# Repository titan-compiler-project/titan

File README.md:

# Titan

Visit the docs at https://titan-compiler-project.github.io/titan/ for more information.

Please look at ``CITATION.cff`` or the citation tools on GitHub for how to cite this repository properly :)

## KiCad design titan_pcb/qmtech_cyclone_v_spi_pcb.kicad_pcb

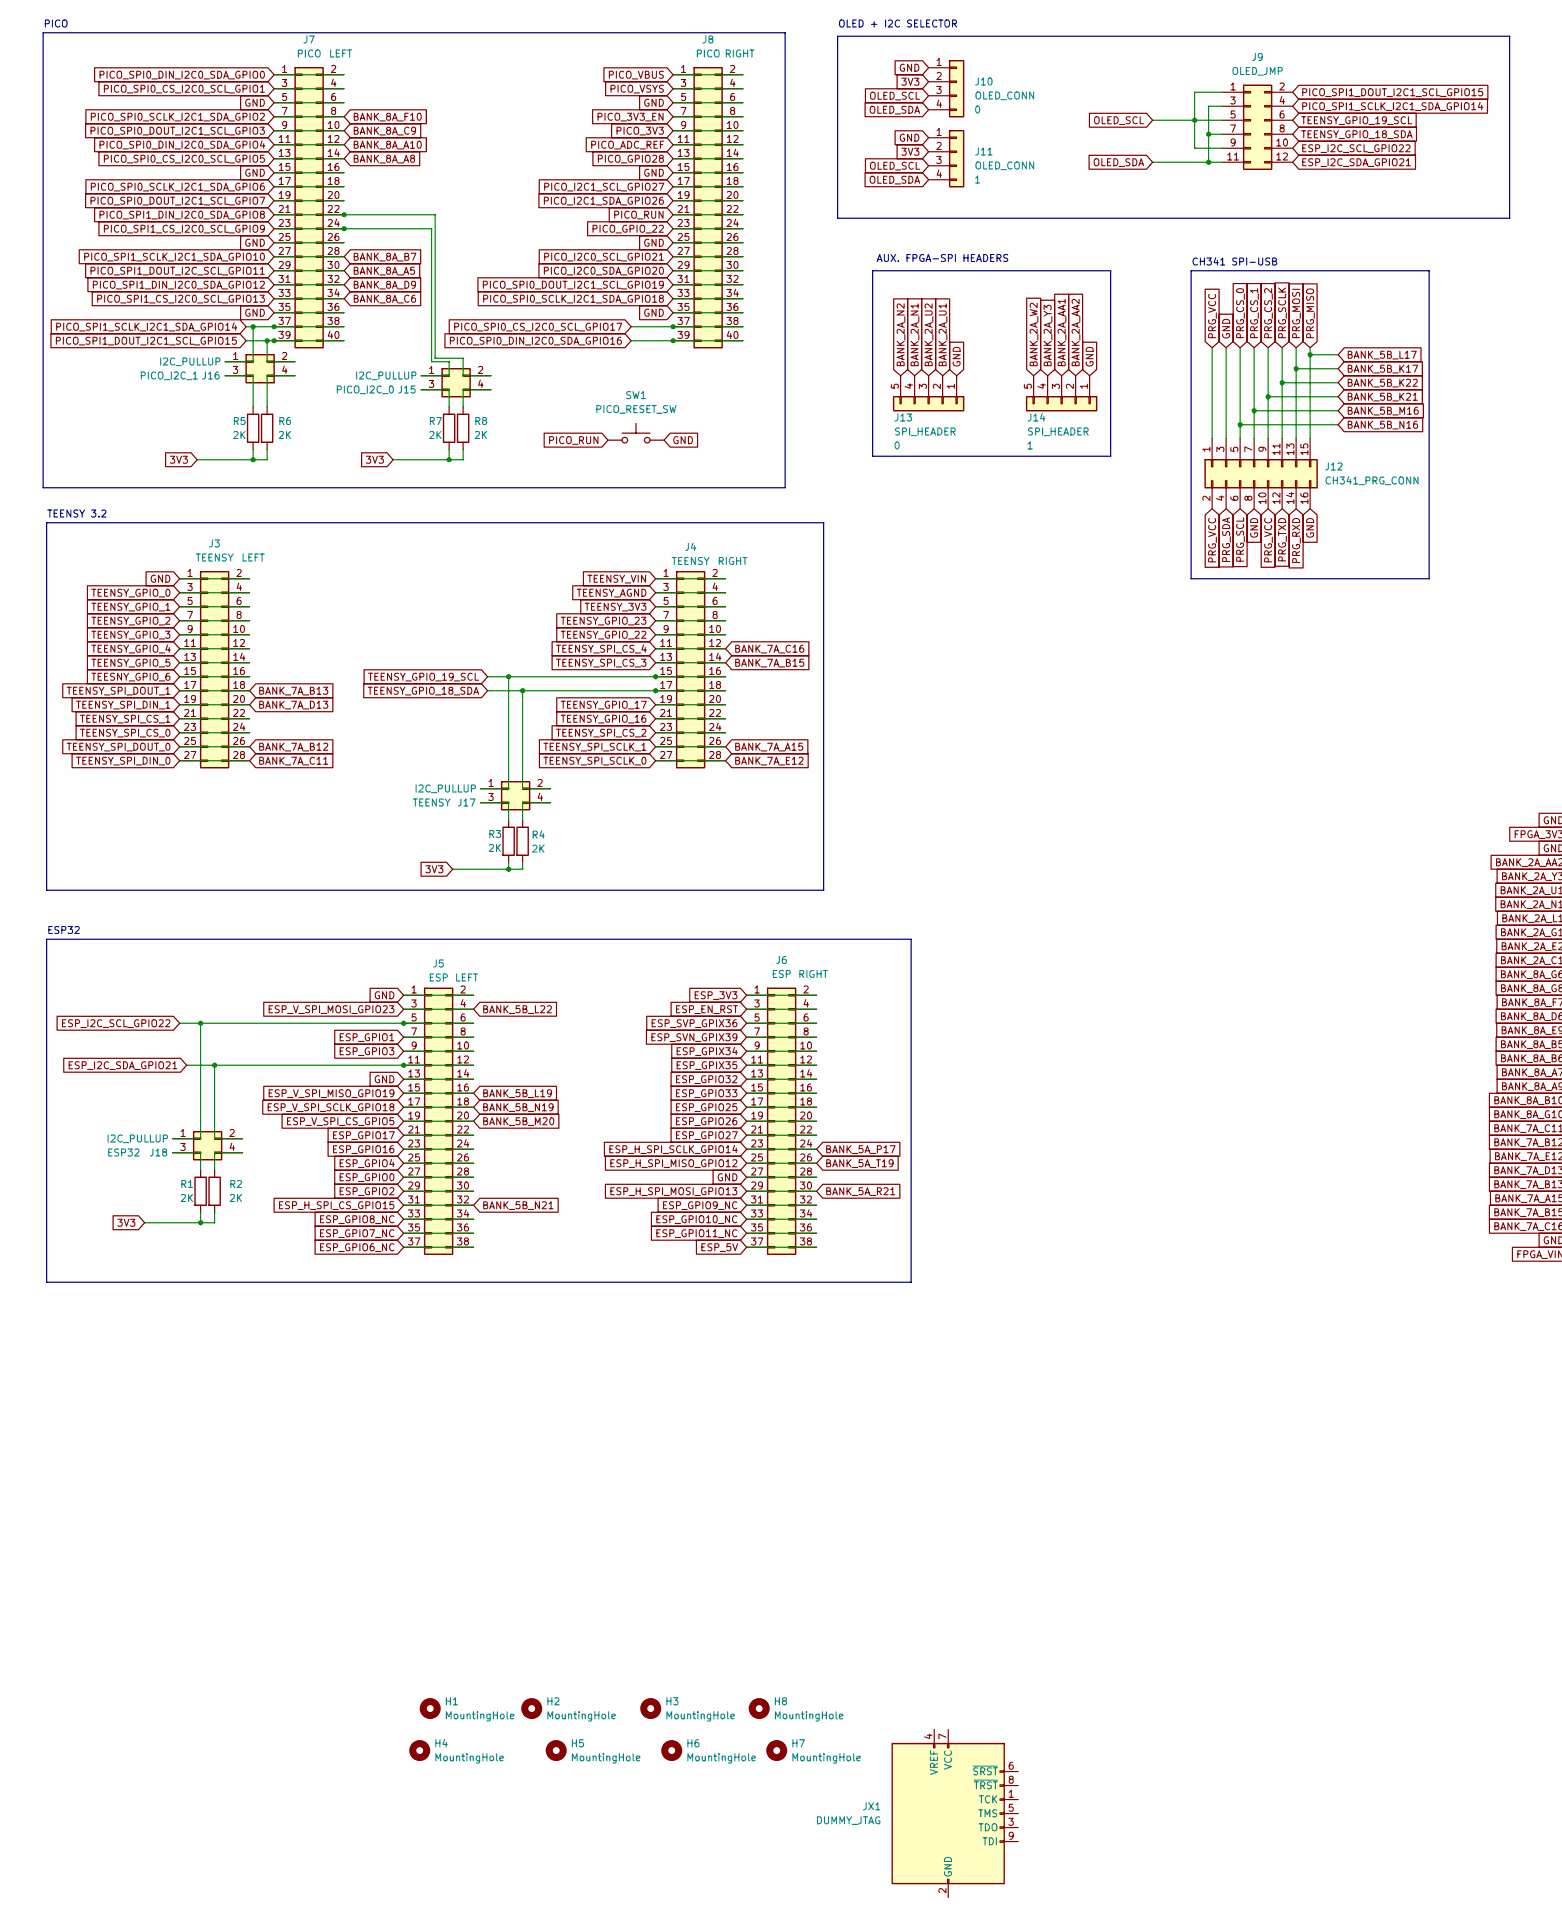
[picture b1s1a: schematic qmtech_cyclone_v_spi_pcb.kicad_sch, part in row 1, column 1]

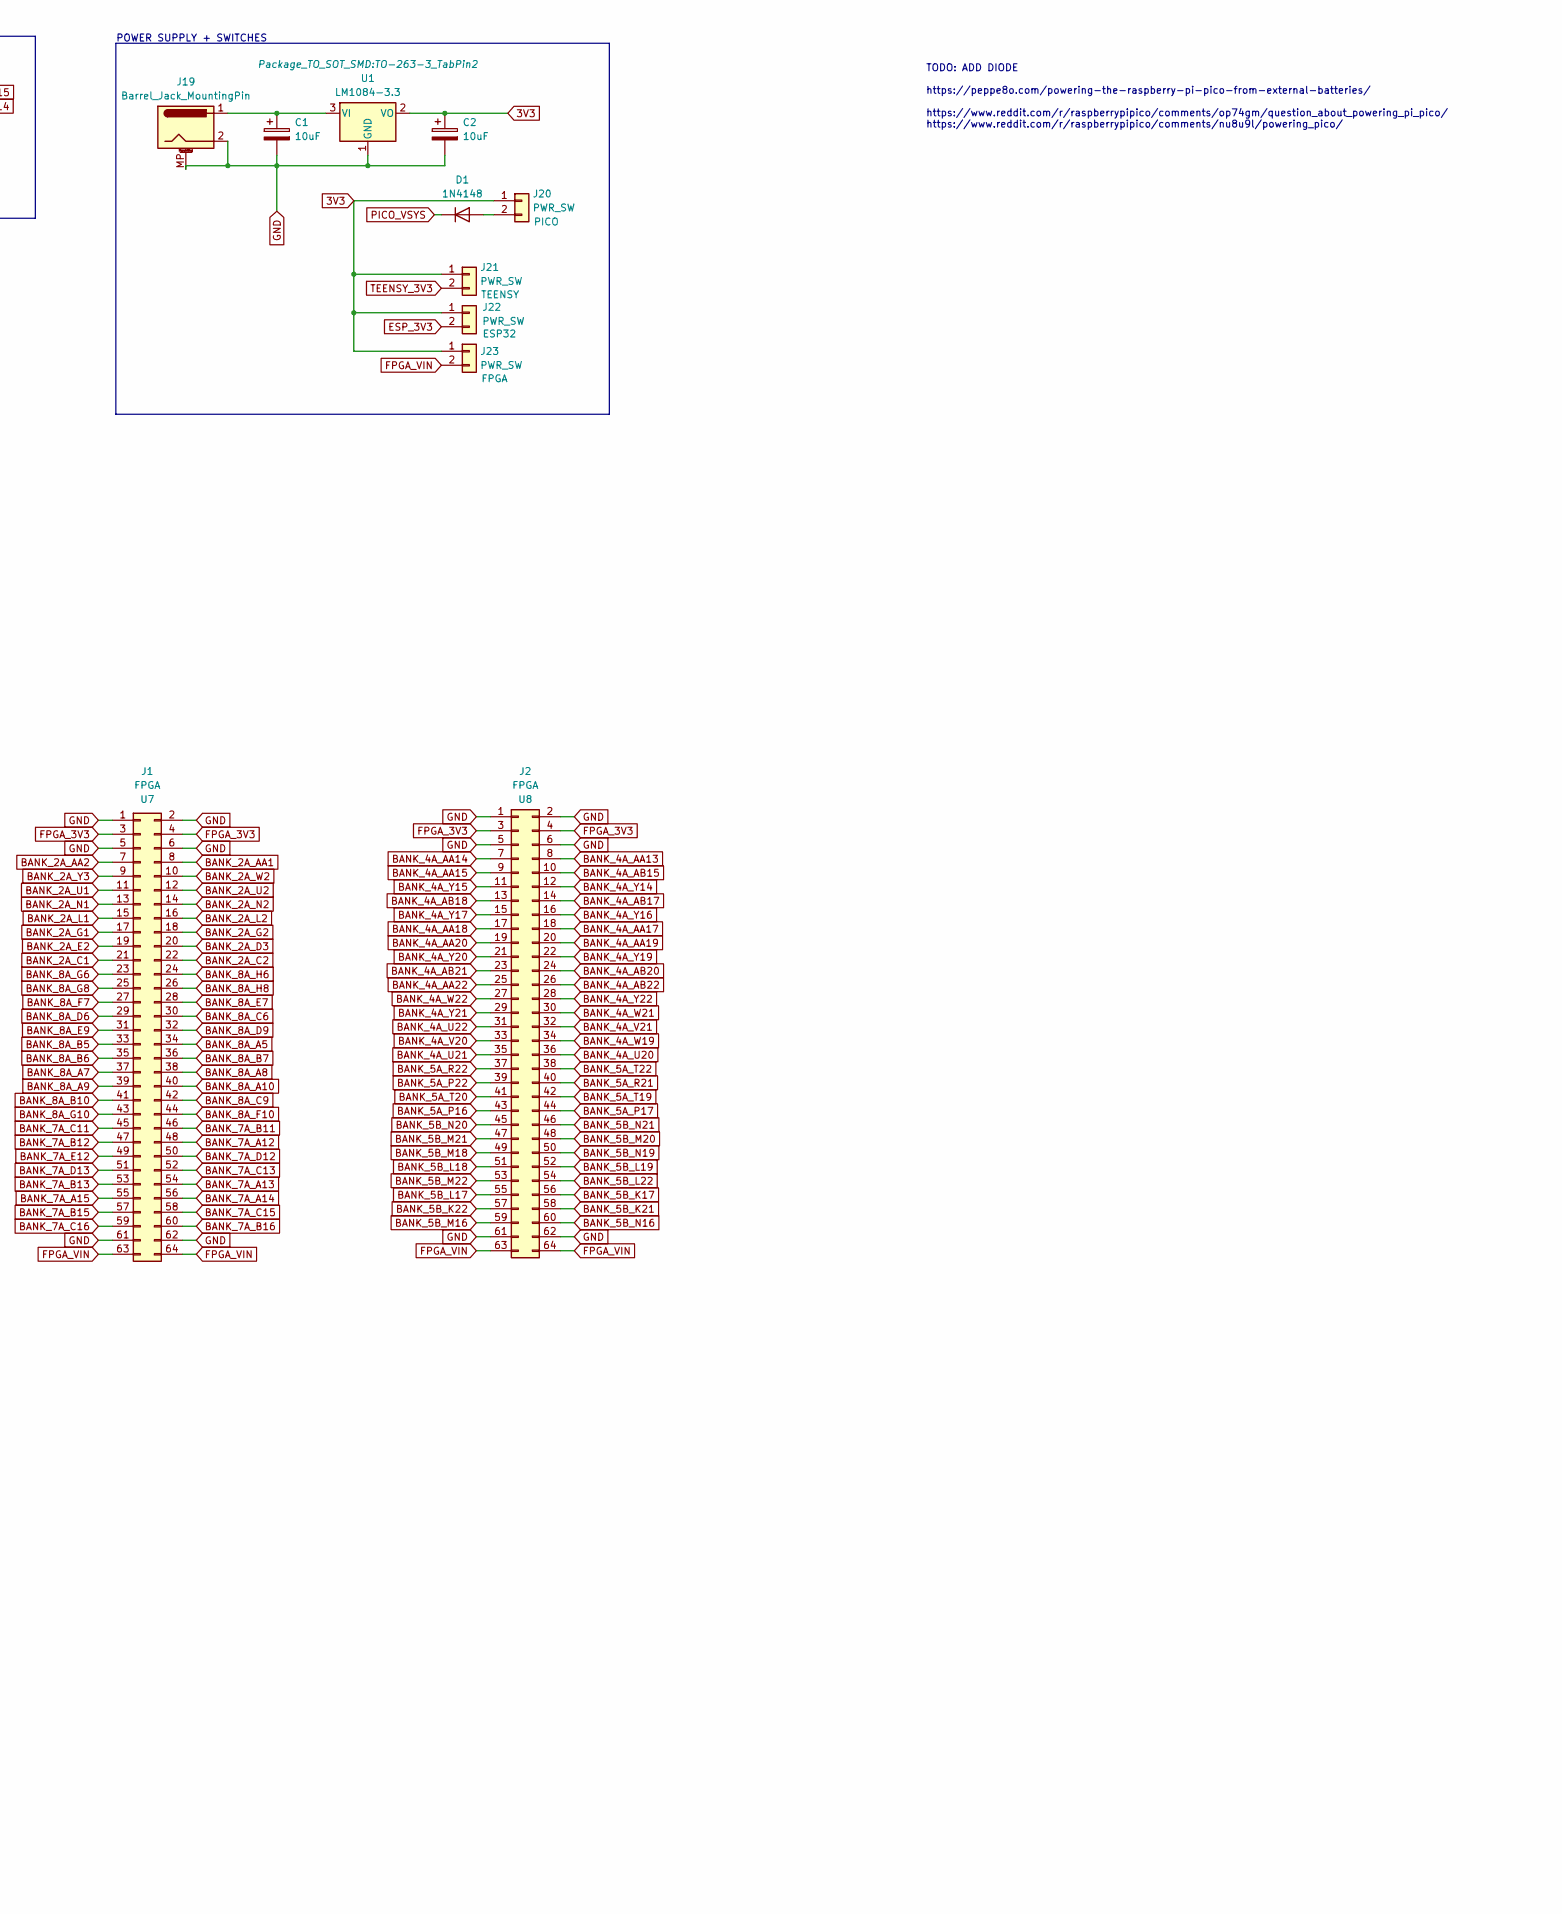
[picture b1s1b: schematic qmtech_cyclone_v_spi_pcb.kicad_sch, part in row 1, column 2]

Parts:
C1, C2: 10uF; CP_EIA-3216-18_Kemet-A_Pad1.58x1.35mm_HandSolder
D1: 1N4148; D_DO-35_SOD27_P7.62mm_Horizontal
H1, H2, H3, H4, H5, H6, H7, H8: MountingHole; MountingHole_2.2mm_M2_ISO7380_Pad_TopBottom
J1, J2: FPGA; PinHeader_2x32_P2.54mm_Vertical
J3, J4: TEENSY; PinSocket_2x14_P2.54mm_Vertical
J5, J6: ESP; PinSocket_2x19_P2.54mm_Vertical
J7, J8: PICO; PinSocket_2x20_P2.54mm_Vertical
J9: OLED_JMP; PinHeader_2x06_P2.54mm_Vertical
J10, J11: OLED_CONN; PinSocket_1x04_P2.54mm_Vertical
J12: CH341_PRG_CONN; PinSocket_2x08_P2.54mm_Vertical
J13, J14: SPI_HEADER; PinHeader_1x05_P2.54mm_Vertical
J15, J16, J17, J18: I2C_PULLUP; PinHeader_2x02_P2.54mm_Vertical
J19: Barrel_Jack_MountingPin; BarrelJack_CUI_PJ-063AH_Horizontal
J20, J21, J22, J23: PWR_SW; PinHeader_1x02_P2.54mm_Vertical
JX1: DUMMY_JTAG; IDC-Header_2x05_P2.54mm_Vertical
R1, R2, R3, R4, R5, R6, R7, R8: 2K; R_1206_3216Metric_Pad1.30x1.75mm_HandSolder
SW1: PICO_RESET_SW; SW_PUSH_6mm_H5mm
U1: LM1084-3.3; TO-263-3_TabPin2

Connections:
3V3: C2.1, J10.2, J11.2, J20.1, J21.1, J22.1, J23.1, R1.2, R2.2, R3.2, R4.2, R5.2, R6.2, R7.2, R8.2, U1.2 (VO)
BANK_2A_AA1: J1.8, J14.3
BANK_2A_AA2: J1.7, J14.2
BANK_2A_C1: J1.21
BANK_2A_C2: J1.22
BANK_2A_D3: J1.20
BANK_2A_E2: J1.19
BANK_2A_G1: J1.17
BANK_2A_G2: J1.18
BANK_2A_L1: J1.15
BANK_2A_L2: J1.16
BANK_2A_N1: J1.13, J13.4
BANK_2A_N2: J1.14, J13.5
BANK_2A_U1: J1.11, J13.2
BANK_2A_U2: J1.12, J13.3
BANK_2A_W2: J1.10, J14.5
BANK_2A_Y3: J1.9, J14.4
BANK_4A_AA13: J2.8
BANK_4A_AA14: J2.7
BANK_4A_AA15: J2.9
BANK_4A_AA17: J2.18
BANK_4A_AA18: J2.17
BANK_4A_AA19: J2.20
BANK_4A_AA20: J2.19
BANK_4A_AA22: J2.25
BANK_4A_AB15: J2.10
BANK_4A_AB17: J2.14
BANK_4A_AB18: J2.13
BANK_4A_AB20: J2.24
BANK_4A_AB21: J2.23
BANK_4A_AB22: J2.26
BANK_4A_U20: J2.36
BANK_4A_U21: J2.35
BANK_4A_U22: J2.31
BANK_4A_V20: J2.33
BANK_4A_V21: J2.32
BANK_4A_W19: J2.34
BANK_4A_W21: J2.30
BANK_4A_W22: J2.27
BANK_4A_Y14: J2.12
BANK_4A_Y15: J2.11
BANK_4A_Y16: J2.16
BANK_4A_Y17: J2.15
BANK_4A_Y19: J2.22
BANK_4A_Y20: J2.21
BANK_4A_Y21: J2.29
BANK_4A_Y22: J2.28
BANK_5A_P16: J2.43
BANK_5A_P17: J2.44, J6.23, J6.24
BANK_5A_P22: J2.39
BANK_5A_R21: J2.40, J6.29, J6.30
BANK_5A_R22: J2.37
BANK_5A_T19: J2.42, J6.25, J6.26
BANK_5A_T20: J2.41
BANK_5A_T22: J2.38
BANK_5B_K17: J2.56, J12.13
BANK_5B_K21: J2.58, J12.9
BANK_5B_K22: J2.57, J12.11
BANK_5B_L17: J2.55, J12.15
BANK_5B_L18: J2.51
BANK_5B_L19: J2.52, J5.15, J5.16
BANK_5B_L22: J2.54, J5.3, J5.4
BANK_5B_M16: J2.59, J12.7
BANK_5B_M18: J2.49
BANK_5B_M20: J2.48, J5.19, J5.20
BANK_5B_M21: J2.47
BANK_5B_M22: J2.53
BANK_5B_N16: J2.60, J12.5
BANK_5B_N19: J2.50, J5.17, J5.18
BANK_5B_N20: J2.45
BANK_5B_N21: J2.46, J5.31, J5.32
BANK_7A_A12: J1.48
BANK_7A_A13: J1.54
BANK_7A_A14: J1.56
BANK_7A_A15: J1.55, J4.25, J4.26
BANK_7A_B11: J1.46
BANK_7A_B12: J1.47, J3.25, J3.26
BANK_7A_B13: J1.53, J3.17, J3.18
BANK_7A_B15: J1.57, J4.13, J4.14
BANK_7A_B16: J1.60
BANK_7A_C11: J1.45, J3.27, J3.28
BANK_7A_C13: J1.52
BANK_7A_C15: J1.58
BANK_7A_C16: J1.59, J4.11, J4.12
BANK_7A_D12: J1.50
BANK_7A_D13: J1.51, J3.19, J3.20
BANK_7A_E12: J1.49, J4.27, J4.28
BANK_8A_A5: J1.34, J7.29, J7.30
BANK_8A_A7: J1.37
BANK_8A_A8: J1.38, J7.13, J7.14
BANK_8A_A9: J1.39
BANK_8A_A10: J1.40, J7.11, J7.12
BANK_8A_B5: J1.33
BANK_8A_B6: J1.35
BANK_8A_B7: J1.36, J7.27, J7.28
BANK_8A_B10: J1.41
BANK_8A_C6: J1.30, J7.33, J7.34
BANK_8A_C9: J1.42, J7.9, J7.10
BANK_8A_D6: J1.29
BANK_8A_D9: J1.32, J7.31, J7.32
BANK_8A_E7: J1.28
BANK_8A_E9: J1.31
BANK_8A_F7: J1.27
BANK_8A_F10: J1.44, J7.7, J7.8
BANK_8A_G6: J1.23
BANK_8A_G8: J1.25
BANK_8A_G10: J1.43
BANK_8A_H6: J1.24
BANK_8A_H8: J1.26
ESP_3V3: J6.1, J6.2, J22.2
ESP_5V: J6.37, J6.38
ESP_EN_RST: J6.3, J6.4
ESP_GPIO0: J5.27, J5.28
ESP_GPIO1: J5.7, J5.8
ESP_GPIO2: J5.29, J5.30
ESP_GPIO3: J5.9, J5.10
ESP_GPIO4: J5.25, J5.26
ESP_GPIO6_NC: J5.37, J5.38
ESP_GPIO7_NC: J5.35, J5.36
ESP_GPIO8_NC: J5.33, J5.34
ESP_GPIO9_NC: J6.31, J6.32
ESP_GPIO10_NC: J6.33, J6.34
ESP_GPIO11_NC: J6.35, J6.36
ESP_GPIO16: J5.23, J5.24
ESP_GPIO17: J5.21, J5.22
ESP_GPIO25: J6.17, J6.18
ESP_GPIO26: J6.19, J6.20
ESP_GPIO27: J6.21, J6.22
ESP_GPIO32: J6.13, J6.14
ESP_GPIO33: J6.15, J6.16
ESP_GPIX34: J6.9, J6.10
ESP_GPIX35: J6.11, J6.12
ESP_I2C_SCL_GPIO22: J5.5, J5.6, J9.10, J18.1
ESP_I2C_SDA_GPIO21: J5.11, J5.12, J9.12, J18.2
ESP_SVN_GPIX39: J6.7, J6.8
ESP_SVP_GPIX36: J6.5, J6.6
FPGA_3V3: J1.3, J1.4, J2.3, J2.4
FPGA_VIN: J1.63, J1.64, J2.63, J2.64, J23.2
GND: C1.2, C2.2, J1.1, J1.2, J1.5, J1.6, J1.61, J1.62, J2.1, J2.2, J2.5, J2.6, J2.61, J2.62, J3.1, J3.2, J5.1, J5.2, J5.13, J5.14, J6.27, J6.28, J7.5, J7.6, J7.15, J7.16, J7.25, J7.26, J7.35, J7.36, J8.5, J8.6, J8.15, J8.16, J8.25, J8.26, J8.35, J8.36, J10.1, J11.1, J12.3, J12.8, J12.16, J13.1, J14.1, J19.2, J19.MP (MountPin), SW1.2, U1.1 (GND)
unnamed: D1.2 (A), J20.2
unnamed: J15.3, R7.1
unnamed: J15.4, R8.1
unnamed: J16.3, R5.1
unnamed: J16.4, R6.1
unnamed: J17.3, R3.1
unnamed: J17.4, R4.1
unnamed: J18.3, R1.1
unnamed: J18.4, R2.1
unnamed: JX1.2 (GND), JX1.10 (GND)
unnamed: C1.1, J19.1, U1.3 (VI)
OLED_SCL: J9.1, J9.5, J9.9, J10.3, J11.3
OLED_SDA: J9.3, J9.7, J9.11, J10.4, J11.4
PICO_3V3: J8.9, J8.10
PICO_3V3_EN: J8.7, J8.8
PICO_ADC_REF: J8.11, J8.12
PICO_GPIO28: J8.13, J8.14
PICO_GPIO_22: J8.23, J8.24
PICO_I2C0_SCL_GPIO21: J8.27, J8.28
PICO_I2C0_SDA_GPIO20: J8.29, J8.30
PICO_I2C1_SCL_GPIO27: J8.17, J8.18
PICO_I2C1_SDA_GPIO26: J8.19, J8.20
PICO_RUN: J8.21, J8.22, SW1.1
PICO_SPI0_CS_I2C0_SCL_GPIO1: J7.3, J7.4
PICO_SPI0_CS_I2C0_SCL_GPIO17: J8.37, J8.38
PICO_SPI0_DIN_I2C0_SDA_GPIO0: J7.1, J7.2
PICO_SPI0_DIN_I2C0_SDA_GPIO16: J8.39, J8.40
PICO_SPI0_DOUT_I2C1_SCL_GPIO7: J7.19, J7.20
PICO_SPI0_DOUT_I2C1_SCL_GPIO19: J8.31, J8.32
PICO_SPI0_SCLK_I2C1_SDA_GPIO6: J7.17, J7.18
PICO_SPI0_SCLK_I2C1_SDA_GPIO18: J8.33, J8.34
PICO_SPI1_CS_I2C0_SCL_GPIO9: J7.23, J7.24, J15.1
PICO_SPI1_DIN_I2C0_SDA_GPIO8: J7.21, J7.22, J15.2
PICO_SPI1_DOUT_I2C1_SCL_GPIO15: J7.39, J7.40, J9.2, J16.2
PICO_SPI1_SCLK_I2C1_SDA_GPIO14: J7.37, J7.38, J9.4, J16.1
PICO_VBUS: J8.1, J8.2
PICO_VSYS: D1.1 (K), J8.3, J8.4
PRG_RXD: J12.14
PRG_SCL: J12.6
PRG_SDA: J12.4
PRG_TXD: J12.12
PRG_VCC: J12.1, J12.2, J12.10
TEENSY_3V3: J4.5, J4.6, J21.2
TEENSY_AGND: J4.3, J4.4
TEENSY_GPIO_0: J3.3, J3.4
TEENSY_GPIO_1: J3.5, J3.6
TEENSY_GPIO_2: J3.7, J3.8
TEENSY_GPIO_3: J3.9, J3.10
TEENSY_GPIO_4: J3.11, J3.12
TEENSY_GPIO_5: J3.13, J3.14
TEENSY_GPIO_16: J4.21, J4.22
TEENSY_GPIO_17: J4.19, J4.20
TEENSY_GPIO_18_SDA: J4.17, J4.18, J9.8, J17.2
TEENSY_GPIO_19_SCL: J4.15, J4.16, J9.6, J17.1
TEENSY_GPIO_22: J4.9, J4.10
TEENSY_GPIO_23: J4.7, J4.8
TEENSY_SPI_CS_0: J3.23, J3.24
TEENSY_SPI_CS_1: J3.21, J3.22
TEENSY_SPI_CS_2: J4.23, J4.24
TEENSY_VIN: J4.1, J4.2
TEESNY_GPIO_6: J3.15, J3.16

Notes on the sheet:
ESP32
OLED + I2C SELECTOR
CH341 SPI-USB
TODO: ADD DIODE https://peppe8o.com/powering-the-raspberry-pi-pico-from-external-batteries/ https://www.reddit.com/r/raspberrypipico/comments/op74gm/question_about_powering_pi_pico/ https://www.reddit.com/r/raspberrypipico/comments/nu8u9l/powering_pico/
POWER SUPPLY + SWITCHES
AUX. FPGA-SPI HEADERS
TEENSY 3.2
PICO

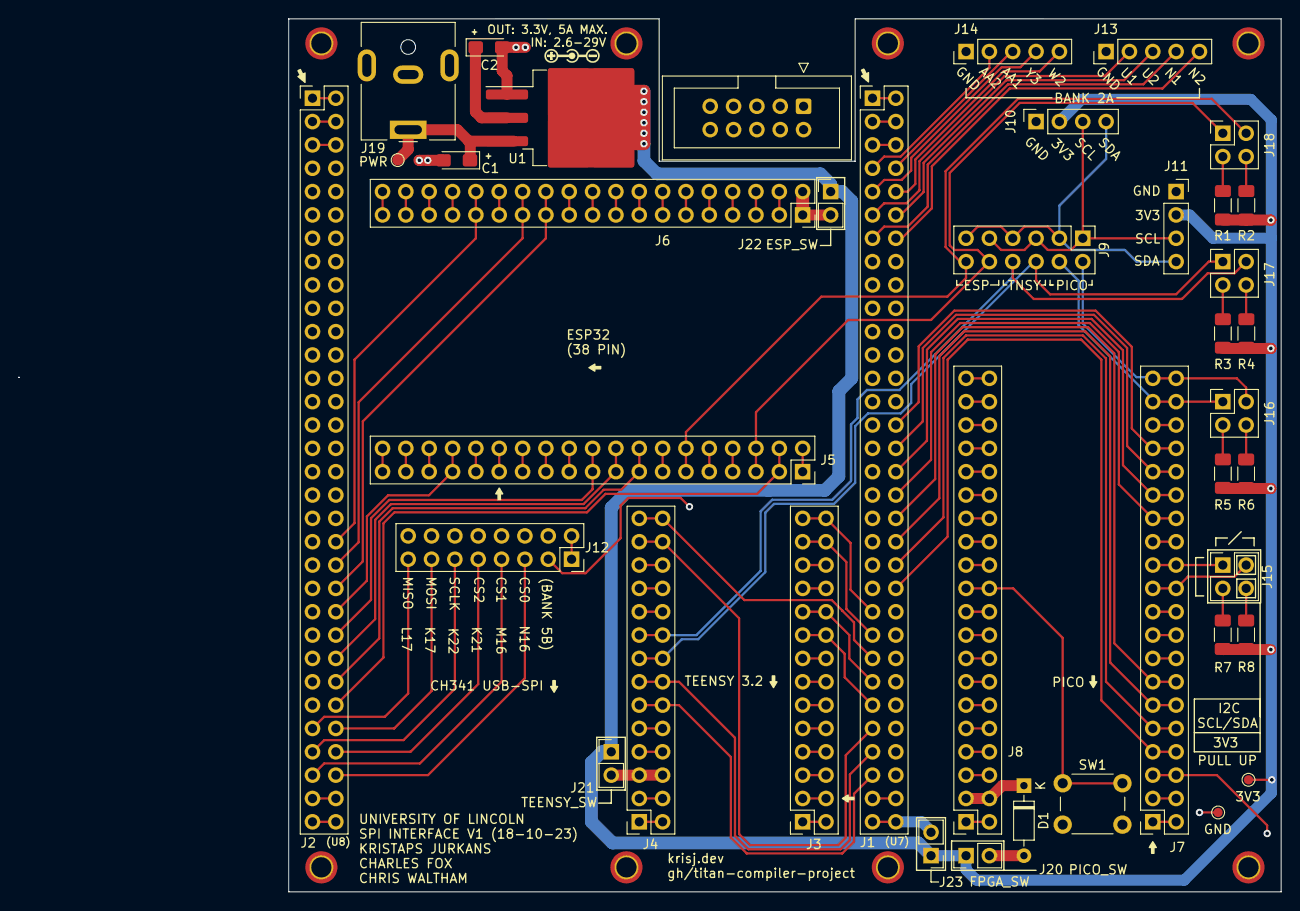
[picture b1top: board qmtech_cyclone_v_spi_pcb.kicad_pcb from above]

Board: 2 copper layers, 137.4 x 95.0 mm, 45 parts (0 on the bottom side), 126 nets.

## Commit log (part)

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2023-03-06 partially working args system, gitignore
2023-03-06 partial options and filename parsing
2023-03-06 added line to add files to list, TODO in parse.py
2023-03-06 removed unnecessary if statements
2023-03-07 added multi-level indentation example
2023-03-07 multi-indent preprocessor kinda working
2023-03-10 updated example
2023-03-10 cleaning up preprocessor
2023-03-10 didn't fully rename vars
2023-03-10 added code to see before and after state of object (for preprocessor)
2023-03-11 added function class to track details
2023-03-11 renamed because its only used for indentation testing
2023-03-11 new test file
2023-03-11 added pyparsing to parse modules, updated main
2023-03-12 updated example with add function
2023-03-12 sepreated add 2 ints example into own file
2023-03-12 updated __init__ for function class
2023-03-12 added SPIRVVM & source, updated gitignore
2023-03-12 changed which property parsed functions get added to, updated main
2023-03-12 added minus assignment
2023-03-13 updated gitignore to ignore .spv binaries
2023-03-13 added more SPIR-V ASM, deleted binaries
2023-03-14 moved grammar to seperate file
2023-03-15 removed in function module declaration, using TitanPythonGrammar directly
2023-03-15 preprocessor now adds semicolons to the end of statements
2023-03-15 WIP symbol table class
2023-03-15 added exception when using not implemented options
2023-03-16 added helper functions for symbol table
2023-03-16 very WIP symbol table implementation
2023-03-19 added auto() to enums
2023-03-21 added enums, updated to auto
2023-03-21 added option to define top module/function
2023-03-21 updated spirv class, added enums for dict keys
2023-03-21 added debug statement dict entry and add_id helper function
2023-03-21 partial spirv generation
2023-03-22 more datatypes
2023-03-22 added spirv function type generation
2023-03-22 renamed enum to better describe section
2023-03-27 moved types out of symbols file, added storage types
2023-03-27 removed non-primative types
2023-03-27 partial rewrite
2023-03-27 ptr type generation working (WIP)
2023-03-28 added get func id helper function
2023-03-28 added const dict and helper functions
2023-03-28 WIP line evaluator
2023-03-28 added int handling for line eval, fixed missing type declarations for OpConstant
2023-03-29 fixed typos
2023-03-30 added ability to track type and id of generated lines
2023-03-30 fixed opcode missing literal function name
2023-03-30 added logic to load variables into temp id when using with arithmetic instructions
2023-04-12 added requirements file
2023-04-12 restructuring project (moving project files to ./titan)
2023-04-12 updated requirements
2023-04-12 added simple unit test for parsing output options
2023-04-16 fixed where options would be ignored after parsing top module filename
2023-04-16 added tests for invalid options and file paths
2023-04-17 moved to test directory
2023-04-17 added some spirv grammar
2023-04-17 partially working spirv grammar, need better seperation
2023-04-18 added grammar test file
2023-04-18 simplified number grammar for python, clarified spirv grammar
2023-04-18 added test for parameter list
2023-04-19 added simple testing of arithmetic grammar
2023-04-19 fixed issue with assignment where function calls would not get parsed
2023-04-20 fixed failing grammar, now will account for function calls in python module body
2023-04-24 updated to ignore *.spvasm files
2023-04-25 added dataflow nodes, and simple unit tests for it
2023-04-27 added type id parameter
2023-04-27 added additional operations
2023-04-27 added another error message
2023-04-27 added tick and update helper functions, modified data structure
2023-04-27 added basic node generation based on parsed spirv, handled by the Verilog_ASM object. updated main to reflect changes.
2023-05-01 updated requirements to include graphviz
2023-05-01 implemented spirv rendering as nodes using graphviz
2023-05-02 updated graphviz generator, added more operations, added ability to update node operation
2023-05-03 added an enum containing sets of operations for easier matching
2023-05-03 removed id slicing when generating list of symbols
2023-05-03 updated code to use newly created operation set
2023-05-04 (WIP) possibly breaking changes - modified generate_dot_graph to ignore tick order for now, added NodeContext return and using that to generate Nodes (but with messed up ticks)
2023-05-07 clarified function parameter names
2023-05-09 updated failing test
2023-05-09 added new example
2023-05-10 updated python grammar to require return type
2023-05-10 updated Function class to retain return type info
2023-05-10 updated example with type hints
2023-05-11 fixed opcode typo, added support for OpSDiv node creation
2023-05-11 added node creation for OpISub and OpIMul
2023-05-14 added simple verilog text generator, updated node context to include in/out in aux data
2023-05-15 added example with 2 operators being used
2023-05-15 added negation, comparison and bitwise operators
2023-05-16 WIP grammar for comparisons/if-else statements
2023-05-16 removed old example
2023-05-17 added example
2023-05-17 added and updated grammar for ternary operator working on assignment
2023-05-17 added comparison operators
2023-05-18 fixed typo, added quick yosys script maker
2023-05-18 added colour to indicate true/false values when creating decision node for dot graph
2023-05-24 reworked how opcodes are generated
2023-06-04 added bitwise shift operators
2023-06-04 bitwise shift example
2023-06-05 added code for remaining comparison operators
2023-06-05 added simple xor checksum generator for sanity
2023-06-05 (WIP) added defs in header, implemented some sections
2023-06-06 defined int24 struct and instructions, modified names, added helper func def
2023-06-06 (WIP) byte extraction from 24 bit address
2023-06-06 fixed incorrect datatype
2023-06-06 defined chip select helpers
2023-06-06 added writing functionality, tested with logic analyser
2023-06-07 added reading function, updated types
2023-06-07 updated types, added more debug info
2023-06-07 added more debug info
2023-06-07 WIP core interface
2023-06-08 fixed syntax errors, testing mem array for params
2023-06-08 both enum syntaxes seem to work fine
2023-06-08 reworked interface, issues with multiple drivers
2023-06-08 updated testbench
2023-06-14 WIP instruction handler on FPGA side + testbench for it
2023-06-14 fixed out of sync counter
2023-06-14 added repeat instruction logic and tx valid pulse
2023-06-18 updated header to add additional instructions and function defs
2023-06-18 testing repeat and transfer instructions (WIP)
2023-07-04 updated gitignore to include kicad
2023-07-04 WIP shield for FPGA to expose many SPI pins
2023-07-04 updated to be sensitive to the FPGA clock instead
2023-07-04 added spi interface for FPGA module, credit to Coert Vonk
2023-07-04 example top module for FPGA, implementing an addition core with SPI interface
2023-07-04 updated read func to use transfer16, removed unnecessary comments
2023-07-04 working example sketch
2023-07-16 WIP reworking python-spirv gen (currently has types, consts, debug info). added new type (None)
2023-07-22 updated instruction enum, added wip core interrupt, updated transfer function
2023-07-24 (WIP) adding bind interrupt instruction to FPGA
2023-07-25 reworked section responsible for buses
2023-07-26 added output to file/string functions, fixed incorrect type gen with floats
2023-07-27 bugfix(ed?) issue where OpSelect would not get correct tick
2023-07-27 added helper function, auto-gen constants if not previously defined
2023-07-27 stripping "%" from id to fix bug (for arithmetic nodes)
2023-08-14 made dimensions nicer, moved screw holes as to not interfer with FPGA
2023-08-18 updated SPIRV function location determination
2023-08-18 cleanup + comments
2023-08-21 (wip) 3v3 supply
2023-08-22 added conditional compilation to support pico & teensy 3.2
2023-08-23 updated silkscreen, added diode for pico power supply, consolidated part value fields for BOM
2023-08-24 moved directory
2023-08-31 added two new instructions, added support for streaming, updated opcodes
2023-09-07 added new folder for testbenches
2023-09-09 removed mcus, updated silkscreen, regenerated bom
2023-09-18 renamed file
2023-09-18 (wip) updated styling
2023-09-18 moved into dedicated rtl folder
2023-09-21 updated gitignore
2023-09-21 added cocotb makefile, testbench for core_interface
2023-09-27 added cocotb testbenche for instruction handler
2023-10-01 added mux module with testbenches, updated test makefile
2023-10-03 fixed non-compiling if statements
2023-10-10 moved into own folder, updated imports where needed
2023-10-10 updated imports
2023-10-10 moved into folder, removed item from set
2023-11-28 wip docs
2023-11-28 updated library refs, added logging
2023-11-28 added logging, partial decorator support, comments
2023-11-28 reg to wire, fixed incorrect index
2023-11-28 added neuron example
2023-11-28 added comment
2023-12-04 Deployed d77e6af with MkDocs version: 1.5.3
2023-12-24 add license, doc files, update doc config
2023-12-24 Deployed bfe872a with MkDocs version: 1.5.3
2024-01-08 updated to handle new args
2024-01-08 added doxygen, updated doc appearance, added pcb & comms library docs
2024-01-14 wip templates + template access
2024-01-14 fix doc typo
2024-01-14 replaced poorly named class
2024-01-17 fixed typo
2024-01-17 removed misleading comment
2024-01-17 refactored verilog generation into own class (VerilogAssembler)
2024-01-17 refactored misnamed class (GenerateSPIRVfromAST -> SPIRVAssembler)
2024-01-17 updated to use refactored classes
2024-01-18 removed old docs
2024-01-18 updated docstrings
2024-01-18 removed useless file
2024-01-20 cleaned up requirements.txt, updated gitignore
2024-01-20 fixed bug with comparison node to sv, updated dotgraph gen to support it too
2024-02-02 helper to display AST nodes
2024-02-02 added new option to only run the SPIR-V generation
2024-02-02 wip array support - can define but not slice
2024-02-06 mkdocs pip requirements txt file
2024-02-07 symbols/consts have id fields, partially working subscripting
2024-02-07 added new page for todos
2024-02-08 removed typehint
2024-02-08 forgot parameter for OpAccessChain
2024-02-12 fixed bug with incorrect temp id handling
2024-02-12 seperated argument parsing for unit testing
2024-02-13 updated constant checking, excluded from temp loading
2024-02-13 fixed syntax warning
2024-02-20 added rich library for nice terminal colours
2024-02-21 clean up, tiny refactoring
2024-02-23 added array ops
2024-02-23 updated docstring
2024-02-23 restructured text generation, wip support for internal variables (incl arrays), added OpAccessChain node creation
2024-02-26 wip loading from arrays in sv
2024-02-28 fixed assignment, logic/reg instanciation
2024-02-28 deleted unused copy of function
2024-03-06 added function to get array dimensions from nodes
2024-03-06 added idea
2024-03-06 code clean up
2024-04-24 updated link, added copy button
2024-04-24 updated documentation
2024-04-24 updated docs, outdated references
2024-05-02 added output folder & theme switching for dot diagrams
2024-05-04 compiler args can be accessed via attributes, instead of calls
2024-05-13 added modifiable templates
2024-05-13 added option to selectively generate comms files
2024-08-07 Deployed d1b9c41 with MkDocs version: 1.5.3
2024-09-03 Bump certifi from 2023.11.17 to 2024.7.4 in /docs
    Bumps [certifi](https://github.com/certifi/python-certifi) from 2023.11.17 to 2024.7.4.
    - [Commits](https://github.com/certifi/python-certifi/compare/2023.11.17...2024.07.04)
    ---
    updated-dependencies:
    - dependency-name: certifi
    dependency-type: direct:production
2025-05-03 add required markers for template
    this allows titan to correctly paste sections of code into the output file
2025-05-04 add/update configs for testing, add makefile for easy runs
2025-05-04 add option to generate report
2025-05-04 add clean target to remove files
2025-05-04 add beginnings of test_node.py
2025-05-05 add __init__.py for mkdocs
2025-05-05 add tests for Node and NodeContext classes
2025-05-05 add tests for NodeAssembler
